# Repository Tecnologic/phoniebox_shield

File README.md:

# phoniebox_shield
 Raspberry Pi Hat for connecting Buttons, LEDs and OnOff SHIM

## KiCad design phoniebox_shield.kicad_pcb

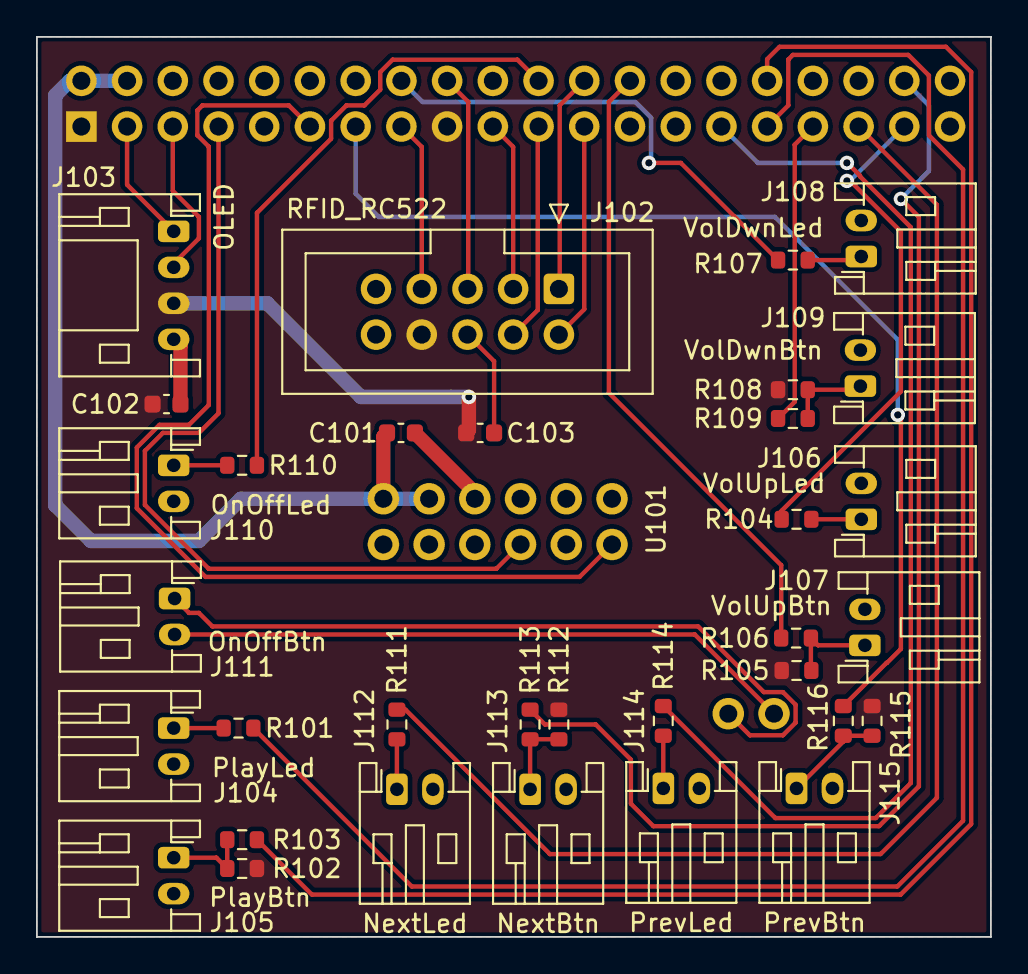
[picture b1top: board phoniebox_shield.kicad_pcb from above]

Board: 2 copper layers, 53.0 x 50.0 mm, 35 parts (1 on the bottom side), 37 nets.

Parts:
C101, C102, C103: 100n; C_0603_1608Metric
J101: GPIO_HEADER; PinSocket_2x20_P2.54mm_Vertical
J102: RFID_RC522; IDC-Header_2x05_P2.54mm_Vertical
J103: OLED; JST_PH_S4B-PH-K_1x04_P2.00mm_Horizontal
J104: PlayLed; JST_PH_S2B-PH-K_1x02_P2.00mm_Horizontal
J105: PlayBtn; JST_PH_S2B-PH-K_1x02_P2.00mm_Horizontal
J106: VolUpLed; JST_PH_S2B-PH-K_1x02_P2.00mm_Horizontal
J107: VolUpBtn; JST_PH_S2B-PH-K_1x02_P2.00mm_Horizontal
J108: VolDwnLed; JST_PH_S2B-PH-K_1x02_P2.00mm_Horizontal
J109: VolDwnBtn; JST_PH_S2B-PH-K_1x02_P2.00mm_Horizontal
J110: OnOffLed; JST_PH_S2B-PH-K_1x02_P2.00mm_Horizontal
J111: OnOffBtn; JST_PH_S2B-PH-K_1x02_P2.00mm_Horizontal
J112: NextLed; JST_PH_S2B-PH-K_1x02_P2.00mm_Horizontal
J113: NextBtn; JST_PH_S2B-PH-K_1x02_P2.00mm_Horizontal
J114: PrevLed; JST_PH_S2B-PH-K_1x02_P2.00mm_Horizontal
J115: PrevBtn; JST_PH_S2B-PH-K_1x02_P2.00mm_Horizontal
R101, R103, R104, R106, R107, R109, R110, R111, R113, R114, R116: 100R; R_0603_1608Metric
R102, R105, R108, R112, R115: 10k; R_0603_1608Metric
U101: OnOffShim

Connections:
+3V3: C102.1, C103.1, J101.1 (3V3), J101.17 (3V3), J102.8, J103.3, R102.1, R105.1, R108.1, R112.1, R115.1
+5V: C101.1, J101.2 (5V), J101.4 (5V), U101.1 (+5V), U101.2 (+5V)
/IRQ: J101.18 (GPIO24), J102.5
/MISO: J101.21 (MISO0/GPIO9), J102.4
/MOSI: J101.19 (MOSI0/GPIO10), J102.3
/RST: J101.15 (GPIO22), J102.7
/SCL: J101.5 (SCL/GPIO3), J103.2
/SCLK: J101.23 (SCLK0/GPIO11), J102.2
/SDA: J101.3 (SDA/GPIO2), J103.1
/\CE: J101.24 (~CE0/GPIO8), J102.1
GND: C101.2, C102.2, C103.2, J101.6 (GND), J101.9 (GND), J101.14 (GND), J101.20 (GND), J101.25 (GND), J101.30 (GND), J101.34 (GND), J101.39 (GND), J102.6, J103.4, J104.2, J105.2, J106.2, J107.2, J108.2, J109.2, J110.2, J112.2, J113.2, J114.2, J115.2, U101.3 (GND), U101.11 (GND)
NEXT_BTN: J101.38 (GPIO20/MOSI1), R113.1
NEXT_LED: J101.35 (GPIO19/MISO1), R111.1
unnamed: J101.7 (GCLK0/GPIO4), U101.10 (Cut_Power)
unnamed: J101.11 (GPIO17), U101.12 (Trigger)
unnamed: J104.1, R101.2
unnamed: J105.1, R102.2, R103.2
unnamed: J106.1, R104.2
unnamed: J107.1, R105.2, R106.2
unnamed: J108.1, R107.2
unnamed: J109.1, R108.2, R109.2
unnamed: J110.1, R110.2
unnamed: J111.1, U101.14 (BTN)
unnamed: J111.2, U101.13 (BTN)
unnamed: J112.1, R111.2
unnamed: J113.1, R112.2, R113.2
unnamed: J114.1, R114.2
unnamed: J115.1, R115.2, R116.2
PLAY_BTN: J101.32 (PWM0/GPIO12), R103.1
PLAY_LED: J101.31 (GCLK2/GPIO6), R101.1
PREV_BTN: J101.13 (GPIO27), R116.1
PREV_LED: J101.29 (GCLK1/GPIO5), R114.1
PWR_LED: J101.22 (GPIO25), R110.1
VOL_DWN_BTN: J101.33 (PWM1/GPIO13), R109.1
VOL_DWN_LED: J101.16 (GPIO23), R107.1
VOL_UP_BTN: J101.26 (~CE1/GPIO7), R106.1
VOL_UP_LED: J101.37 (GPIO26), R104.1
